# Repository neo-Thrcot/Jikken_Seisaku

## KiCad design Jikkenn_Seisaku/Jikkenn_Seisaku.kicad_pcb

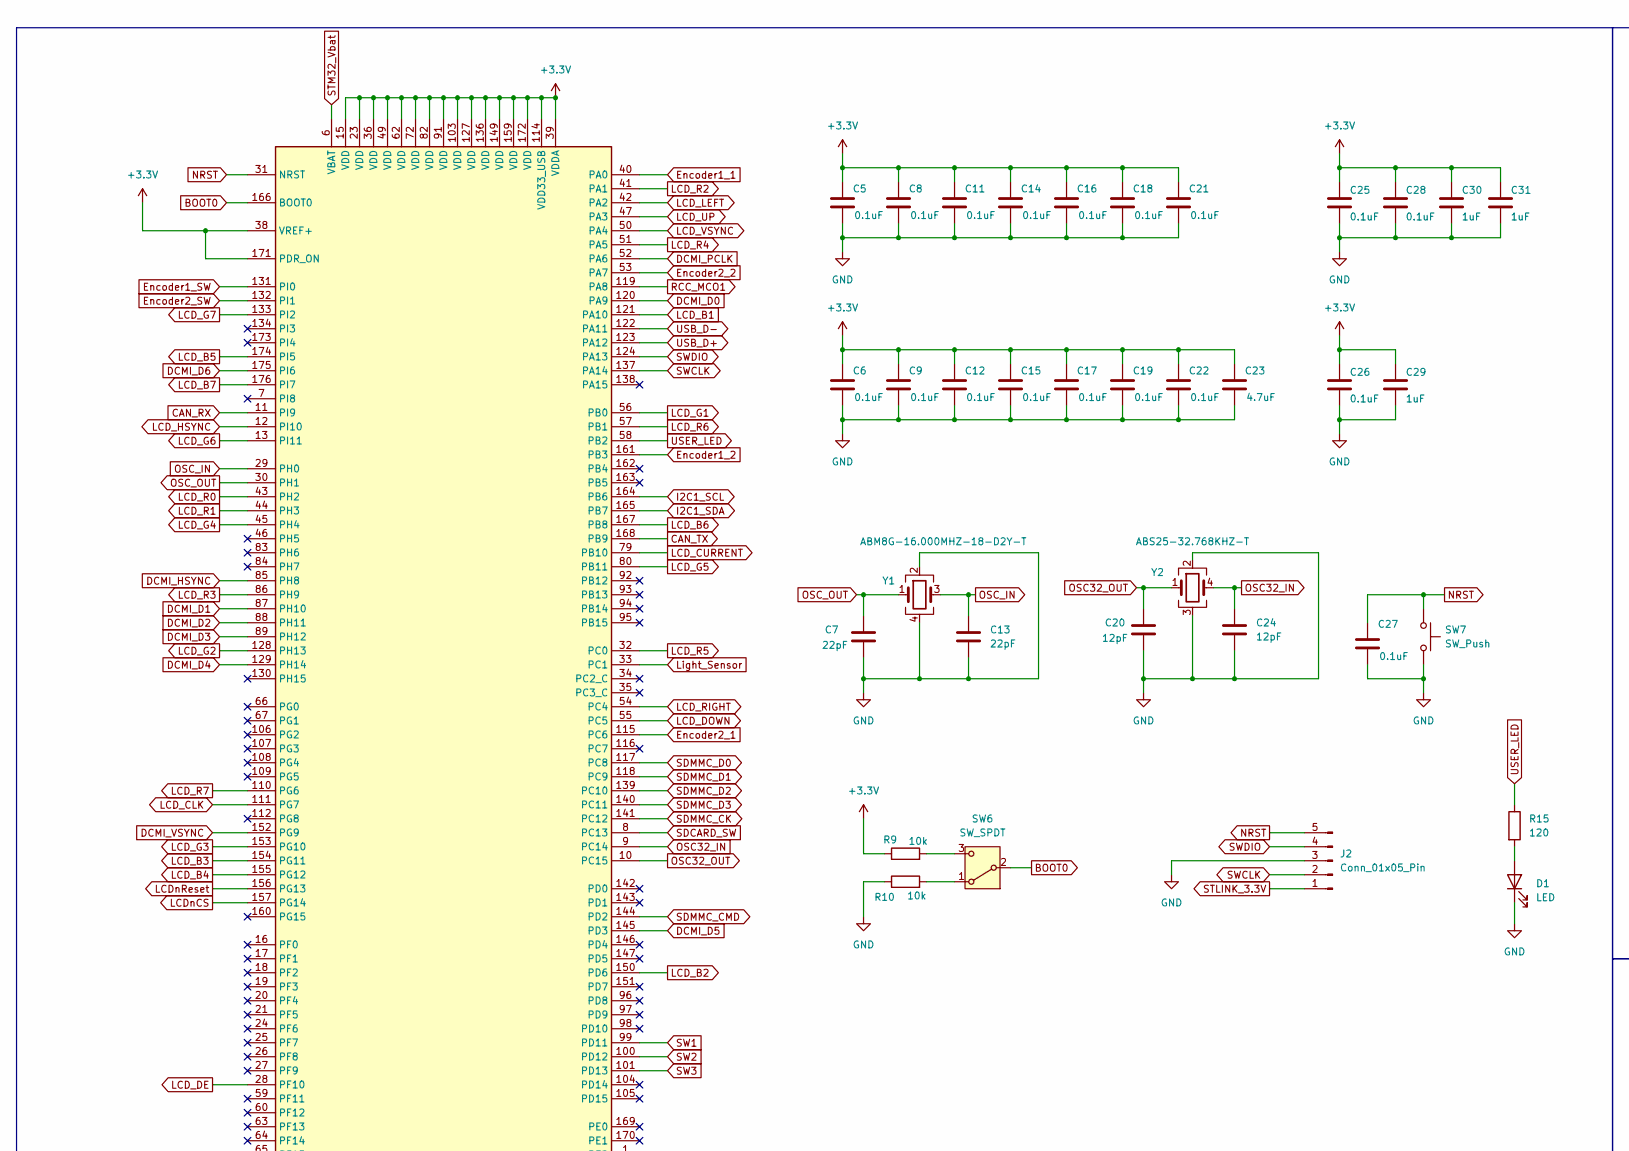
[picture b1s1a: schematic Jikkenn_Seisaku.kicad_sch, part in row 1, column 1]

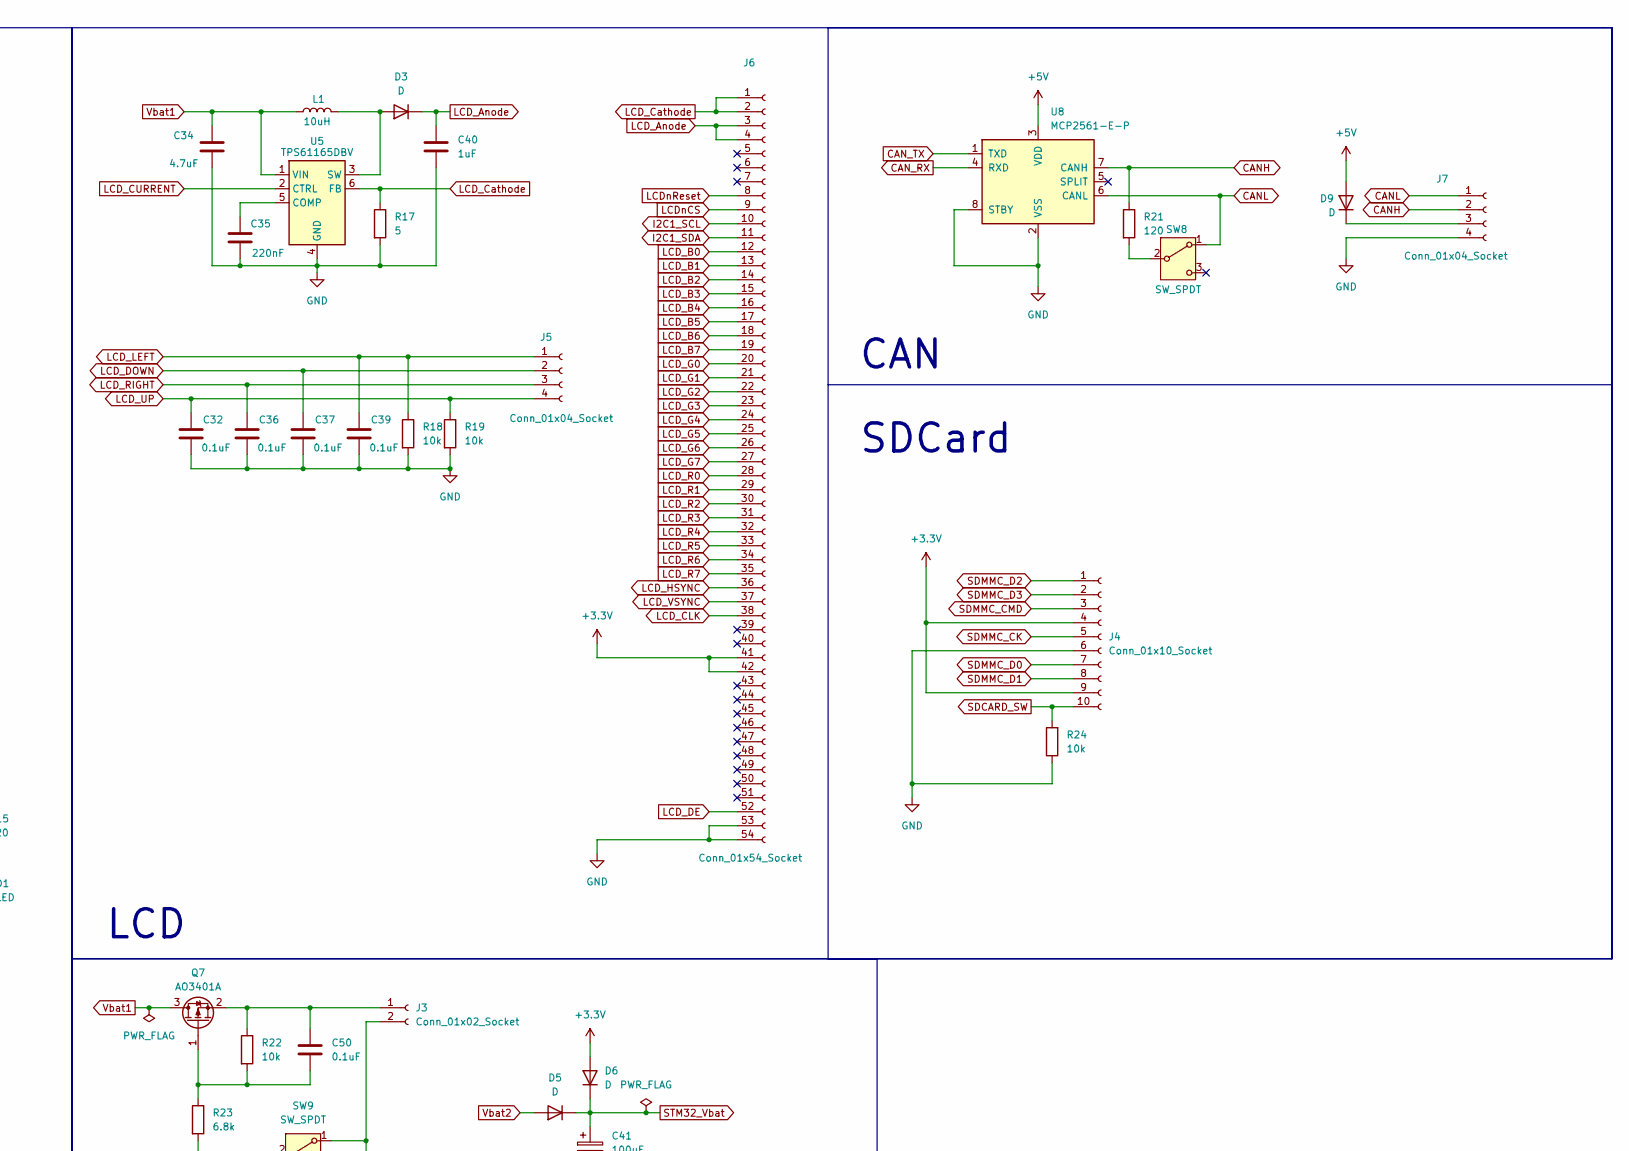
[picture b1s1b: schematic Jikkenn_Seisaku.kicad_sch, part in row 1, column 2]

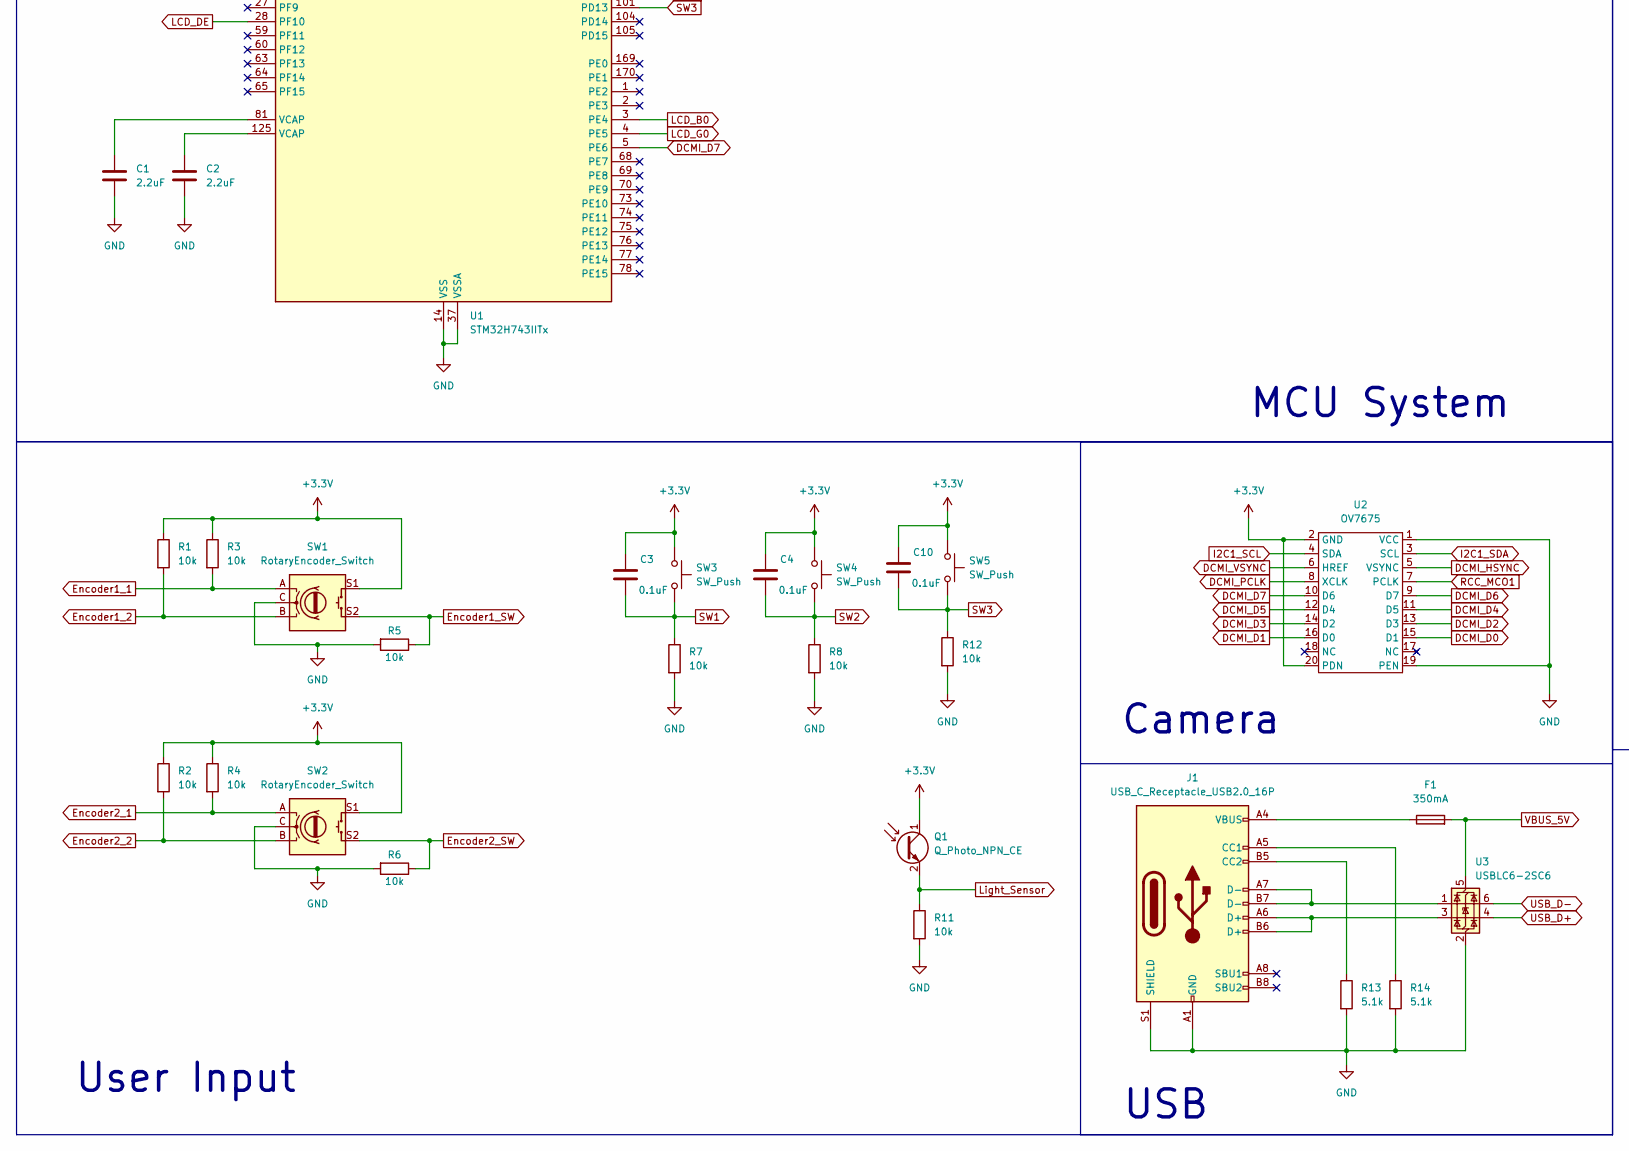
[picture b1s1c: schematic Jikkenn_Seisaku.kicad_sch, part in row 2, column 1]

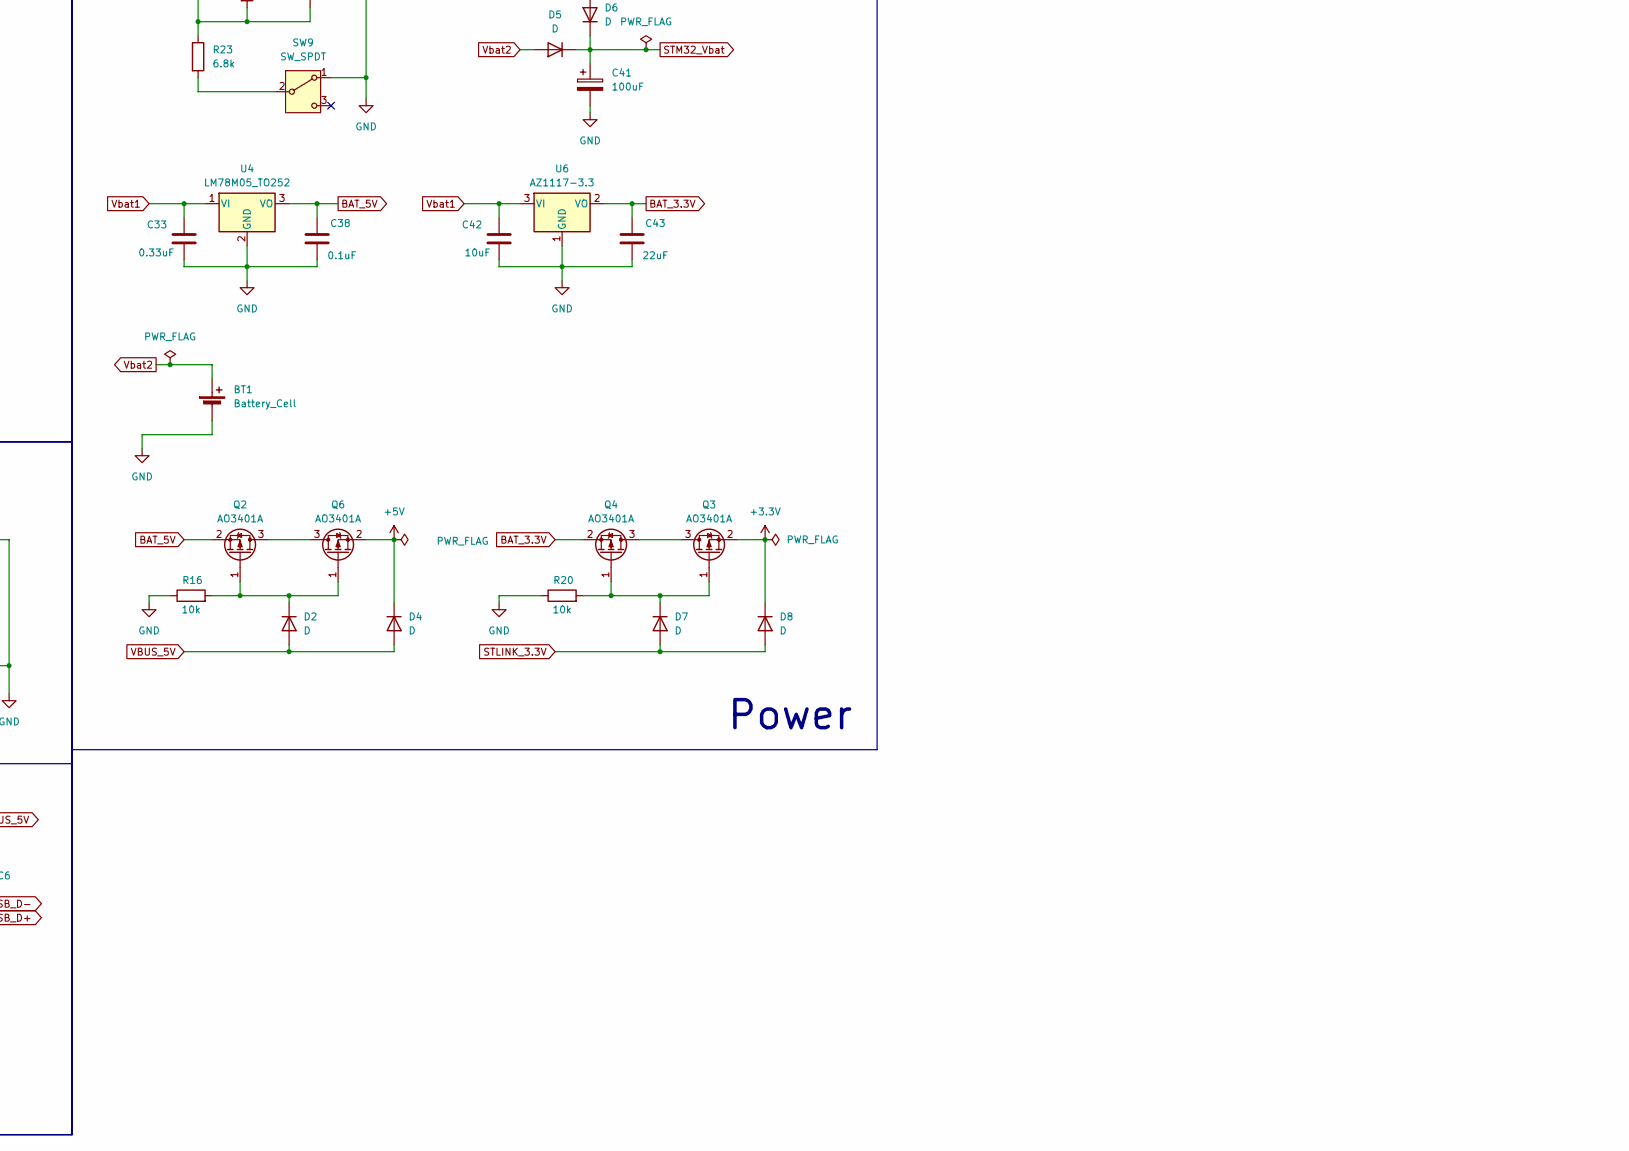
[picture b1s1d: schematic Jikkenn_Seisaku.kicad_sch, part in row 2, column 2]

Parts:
BT1: Battery_Cell; BatteryHolder_MYOUNG_BS-07-A1BJ001_CR2032
C1, C2: 2.2uF; C_0603_1608Metric_Pad1.08x0.95mm_HandSolder
C3, C4, C5, C6, C8, C9, C10, C11, C12, C14, C15, C16, C17, C18, C19, C21, C22, C25, C26, C27, C28, C32, C36, C37, C38, C39, C50: 0.1uF; C_0603_1608Metric_Pad1.08x0.95mm_HandSolder
C7, C13: 22pF; C_0603_1608Metric_Pad1.08x0.95mm_HandSolder
C20, C24: 12pF; C_0603_1608Metric_Pad1.08x0.95mm_HandSolder
C23, C34: 4.7uF; C_0603_1608Metric_Pad1.08x0.95mm_HandSolder
C29, C30, C31, C40: 1uF; C_0603_1608Metric_Pad1.08x0.95mm_HandSolder
C33: 0.33uF; C_0603_1608Metric_Pad1.08x0.95mm_HandSolder
C35: 220nF; C_0603_1608Metric_Pad1.08x0.95mm_HandSolder
C41: 100uF; CP_Elec_6.3x5.4_Nichicon
C42: 10uF; C_0603_1608Metric_Pad1.08x0.95mm_HandSolder
C43: 22uF; C_0603_1608Metric_Pad1.08x0.95mm_HandSolder
D1: LED; LED_0603_1608Metric_Pad1.05x0.95mm_HandSolder
D2, D3, D4, D5, D6, D7, D8, D9: D; D_TUMD2
F1: 350mA; Fuse_2010_5025Metric_Pad1.52x2.65mm_HandSolder
J1: USB_C_Receptacle_USB2.0_16P; USB_C_Receptacle_XKB_U262-16XN-4BVC11
J2: Conn_01x05_Pin; JST_XH_S5B-XH-A-1_1x05_P2.50mm_Horizontal
J3: Conn_01x02_Socket; JST_XH_S2B-XH-A_1x02_P2.50mm_Horizontal
J4: Conn_01x10_Socket; PinSocket_1x10_P2.54mm_Vertical
J5: Conn_01x04_Socket; Molex_200528-0040_1x04-1MP_P1.00mm_Horizontal
J6: Conn_01x54_Socket; Amphenol_F32Q-1A7x1-11054_1x54-1MP_P0.5mm_Horizontal
J7: Conn_01x04_Socket; JST_XH_S4B-XH-A-1_1x04_P2.50mm_Horizontal
L1: 10uH; LQH43PN100M26L
Q1: Q_Photo_NPN_CE; NJL7502
Q2, Q3, Q4, Q6, Q7: AO3401A; SOT-23
R1, R2, R3, R4, R5, R6, R7, R8, R9, R10, R11, R12, R16, R18, R19, R20, R22, R24: 10k; R_0603_1608Metric_Pad0.98x0.95mm_HandSolder
R13, R14: 5.1k; R_0603_1608Metric_Pad0.98x0.95mm_HandSolder
R15, R21: 120; R_0603_1608Metric_Pad0.98x0.95mm_HandSolder
R17: 5; R_0603_1608Metric_Pad0.98x0.95mm_HandSolder
R23: 6.8k; R_0603_1608Metric_Pad0.98x0.95mm_HandSolder
SW1, SW2: RotaryEncoder_Switch; RE111F-4S1-152S4-15P-A
SW3, SW4, SW5, SW7: SW_Push; SW_PUSH_6mm
SW6, SW8, SW9: SW_SPDT; PinSocket_1x03_P2.54mm_Vertical
U1: STM32H743IITx; LQFP-176_24x24mm_P0.5mm
U2: OV7675; PinSocket_2x10_P2.54mm_Vertical
U3: USBLC6-2SC6; SOT-23-6
U4: LM78M05_TO252; TO-252-2
U5: TPS61165DBV; SOT-23-6
U6: AZ1117-3.3; SOT-223-3_TabPin2
U8: MCP2561-E-P; DIP-8_W7.62mm
Y1: ABM8G-16.000MHZ-18-D2Y-T; Crystal_SMD_Abracon_ABM8G-4Pin_3.2x2.5mm
Y2: ABS25-32.768KHZ-T; Crystal_SMD_Abracon_ABS25-4Pin_8.0x3.8mm

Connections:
+3.3V: C3.1, C4.1, C5.1, C6.1, C8.1, C9.1, C10.1, C11.1, C12.1, C14.1, C15.1, C16.1, C17.1, C18.1, C19.1, C21.1, C22.1, C23.1, C25.1, C26.1, C28.1, C29.1, C30.1, C31.1, D6.2 (A), D8.1 (K), J4.4, J4.9, J6.41, J6.42, Q1.1 (C), Q3.2 (S), R1.1, R2.1, R3.1, R4.1, R9.1, SW1.S1, SW2.S1, SW3.1, SW4.1, SW5.1, U1.15 (VDD), U1.23 (VDD), U1.36 (VDD), U1.38 (VREF+), U1.39 (VDDA), U1.49 (VDD), U1.62 (VDD), U1.72 (VDD), U1.82 (VDD), U1.91 (VDD), U1.103 (VDD), U1.114 (VDD33_USB), U1.127 (VDD), U1.136 (VDD), U1.149 (VDD), U1.159 (VDD), U1.171 (PDR_ON), U1.172 (VDD), U2.2 (GND), U2.20 (PDN)
+5V: D4.1 (K), D9.2 (A), Q6.2 (S), U8.3 (VDD)
BAT_3.3V: C43.1, Q4.2 (S), U6.2 (VO)
BAT_5V: C38.1, Q2.2 (S), U4.3 (VO)
BOOT0: SW6.2 (B), U1.166 (BOOT0)
CANH: J7.2, R21.1, U8.7 (CANH)
CANL: J7.1, SW8.1 (A), U8.6 (CANL)
CAN_RX: U1.11 (PI9), U8.4 (RXD)
CAN_TX: U1.168 (PB9), U8.1 (TXD)
DCMI_D0: U1.120 (PA9), U2.15 (D1)
DCMI_D1: U1.87 (PH10), U2.16 (D0)
DCMI_D2: U1.88 (PH11), U2.13 (D3)
DCMI_D3: U1.89 (PH12), U2.14 (D2)
DCMI_D4: U1.129 (PH14), U2.11 (D5)
DCMI_D5: U1.145 (PD3), U2.12 (D4)
DCMI_D6: U1.175 (PI6), U2.9 (D7)
DCMI_D7: U1.5 (PE6), U2.10 (D6)
DCMI_HSYNC: U1.85 (PH8), U2.5 (VSYNC)
DCMI_PCLK: U1.52 (PA6), U2.8 (XCLK)
DCMI_VSYNC: U1.152 (PG9), U2.6 (HREF)
Encoder1_1: R3.2, SW1.A, U1.40 (PA0)
Encoder1_2: R1.2, SW1.B, U1.161 (PB3)
Encoder1_SW: R5.1, SW1.S2, U1.131 (PI0)
Encoder2_1: R4.2, SW2.A, U1.115 (PC6)
Encoder2_2: R2.2, SW2.B, U1.53 (PA7)
Encoder2_SW: R6.1, SW2.S2, U1.132 (PI1)
GND: BT1.2 (-), C1.2, C2.2, C5.2, C6.2, C7.2, C8.2, C9.2, C11.2, C12.2, C13.2, C14.2, C15.2, C16.2, C17.2, C18.2, C19.2, C20.2, C21.2, C22.2, C23.2, C24.2, C25.2, C26.2, C27.2, C28.2, C29.2, C30.2, C31.2, C32.2, C33.2, C34.2, C35.2, C36.2, C37.2, C38.2, C39.2, C40.2, C41.2, C42.2, C43.2, D1.1 (K), J1.A1 (GND), J1.A12 (GND), J1.B1 (GND), J1.B12 (GND), J1.S1 (SHIELD), J2.3, J3.2, J4.6, J6.53, J6.54, J7.4, R5.2, R6.2, R7.2, R8.2, R10.1, R11.2, R12.2, R13.2, R14.2, R16.1, R17.2, R18.2, R19.2, R20.1, R24.1, SW1.C, SW2.C, SW7.2, SW9.1 (A), U1.14 (VSS), U1.22 (VSS), U1.37 (VSSA), U1.48 (VSS), U1.61 (VSS), U1.71 (VSS), U1.90 (VSS), U1.102 (VSS), U1.113 (VSS), U1.126 (VSS), U1.135 (VSS), U1.148 (VSS), U1.158 (VSS), U2.1 (VCC), U2.19 (PEN), U3.2 (GND), U4.2 (GND), U5.4 (GND), U6.1 (GND), U8.2 (VSS), U8.8 (STBY), Y1.2, Y1.4, Y2.2, Y2.3
I2C1_SCL: J6.10, U1.164 (PB6), U2.4 (SDA)
I2C1_SDA: J6.11, U1.165 (PB7), U2.3 (SCL)
LCD_Anode: C40.1, D3.1 (K), J6.3, J6.4
LCD_B0: J6.12, U1.3 (PE4)
LCD_B1: J6.13, U1.121 (PA10)
LCD_B2: J6.14, U1.150 (PD6)
LCD_B3: J6.15, U1.154 (PG11)
LCD_B4: J6.16, U1.155 (PG12)
LCD_B5: J6.17, U1.174 (PI5)
LCD_B6: J6.18, U1.167 (PB8)
LCD_B7: J6.19, U1.176 (PI7)
LCD_CLK: J6.38, U1.111 (PG7)
LCD_CURRENT: U1.79 (PB10), U5.2 (CTRL)
LCD_Cathode: J6.1, J6.2, R17.1, U5.6 (FB)
LCD_DE: J6.52, U1.28 (PF10)
LCD_DOWN: C37.1, J5.2, U1.55 (PC5)
LCD_G0: J6.20, U1.4 (PE5)
LCD_G1: J6.21, U1.56 (PB0)
LCD_G2: J6.22, U1.128 (PH13)
LCD_G3: J6.23, U1.153 (PG10)
LCD_G4: J6.24, U1.45 (PH4)
LCD_G5: J6.25, U1.80 (PB11)
LCD_G6: J6.26, U1.13 (PI11)
LCD_G7: J6.27, U1.133 (PI2)
LCD_HSYNC: J6.36, U1.12 (PI10)
LCD_LEFT: C39.1, J5.1, R18.1, U1.42 (PA2)
LCD_R0: J6.28, U1.43 (PH2)
LCD_R1: J6.29, U1.44 (PH3)
LCD_R2: J6.30, U1.41 (PA1)
LCD_R3: J6.31, U1.86 (PH9)
LCD_R4: J6.32, U1.51 (PA5)
LCD_R5: J6.33, U1.32 (PC0)
LCD_R6: J6.34, U1.57 (PB1)
LCD_R7: J6.35, U1.110 (PG6)
LCD_RIGHT: C36.1, J5.3, U1.54 (PC4)
LCD_UP: C32.1, J5.4, R19.1, U1.47 (PA3)
LCD_VSYNC: J6.37, U1.50 (PA4)
LCDnCS: J6.9, U1.157 (PG14)
LCDnReset: J6.8, U1.156 (PG13)
Light_Sensor: Q1.2 (E), R11.1, U1.33 (PC1)
NRST: C27.1, J2.5, SW7.1, U1.31 (NRST)
unnamed: C1.1, U1.81 (VCAP)
unnamed: C2.1, U1.125 (VCAP)
unnamed: D1.2 (A), R15.2
unnamed: D2.1 (K), Q2.1 (G), Q6.1 (G), R16.2
unnamed: D3.2 (A), L1.2, U5.3 (SW)
unnamed: D7.1 (K), Q3.1 (G), Q4.1 (G), R20.2
unnamed: D9.1 (K), J7.3
unnamed: F1.1, J1.A4 (VBUS), J1.A9 (VBUS), J1.B4 (VBUS), J1.B9 (VBUS)
unnamed: J1.A5 (CC1), R14.1
unnamed: J1.B5 (CC2), R13.1
unnamed: J1.A6 (D+), J1.B6 (D+), U3.3 (I/O2)
unnamed: J1.A7 (D-), J1.B7 (D-), U3.1 (I/O1)
unnamed: C50.1, J3.1, Q7.2 (S), R22.1
unnamed: Q2.3 (D), Q6.3 (D)
unnamed: Q3.3 (D), Q4.3 (D)
unnamed: C50.2, Q7.1 (G), R22.2, R23.1
unnamed: R10.2, SW6.1 (A)
unnamed: R9.2, SW6.3 (C)
unnamed: R21.2, SW8.2 (B)
unnamed: R23.2, SW9.2 (B)
unnamed: C35.1, U5.5 (COMP)
OSC32_IN: C24.1, U1.9 (PC14), Y2.4
OSC32_OUT: C20.1, U1.10 (PC15), Y2.1
OSC_IN: C13.1, U1.29 (PH0), Y1.3
OSC_OUT: C7.1, U1.30 (PH1), Y1.1
RCC_MCO1: U1.119 (PA8), U2.7 (PCLK)
SDCARD_SW: J4.10, R24.2, U1.8 (PC13)
SDMMC_CK: J4.5, U1.141 (PC12)
SDMMC_CMD: J4.3, U1.144 (PD2)
SDMMC_D0: J4.7, U1.117 (PC8)
SDMMC_D1: J4.8, U1.118 (PC9)
SDMMC_D2: J4.1, U1.139 (PC10)
SDMMC_D3: J4.2, U1.140 (PC11)
STLINK_3.3V: D7.2 (A), D8.2 (A), J2.1
STM32_Vbat: C41.1, D5.1 (K), D6.1 (K), U1.6 (VBAT)
SW1: C3.2, R7.1, SW3.2, U1.99 (PD11)
SW2: C4.2, R8.1, SW4.2, U1.100 (PD12)
SW3: C10.2, R12.1, SW5.2, U1.101 (PD13)
SWCLK: J2.2, U1.137 (PA14)
SWDIO: J2.4, U1.124 (PA13)
USB_D+: U1.123 (PA12), U3.4 (I/O2)
USB_D-: U1.122 (PA11), U3.6 (I/O1)
USER_LED: R15.1, U1.58 (PB2)
VBUS_5V: D2.2 (A), D4.2 (A), F1.2, U3.5 (VBUS)
Vbat1: C33.1, C34.1, C42.1, L1.1, Q7.3 (D), U4.1 (VI), U5.1 (VIN), U6.3 (VI)
Vbat2: BT1.1 (+), D5.2 (A)

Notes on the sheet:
CAN
Power
User Input
MCU System
LCD
SDCard
USB
Camera

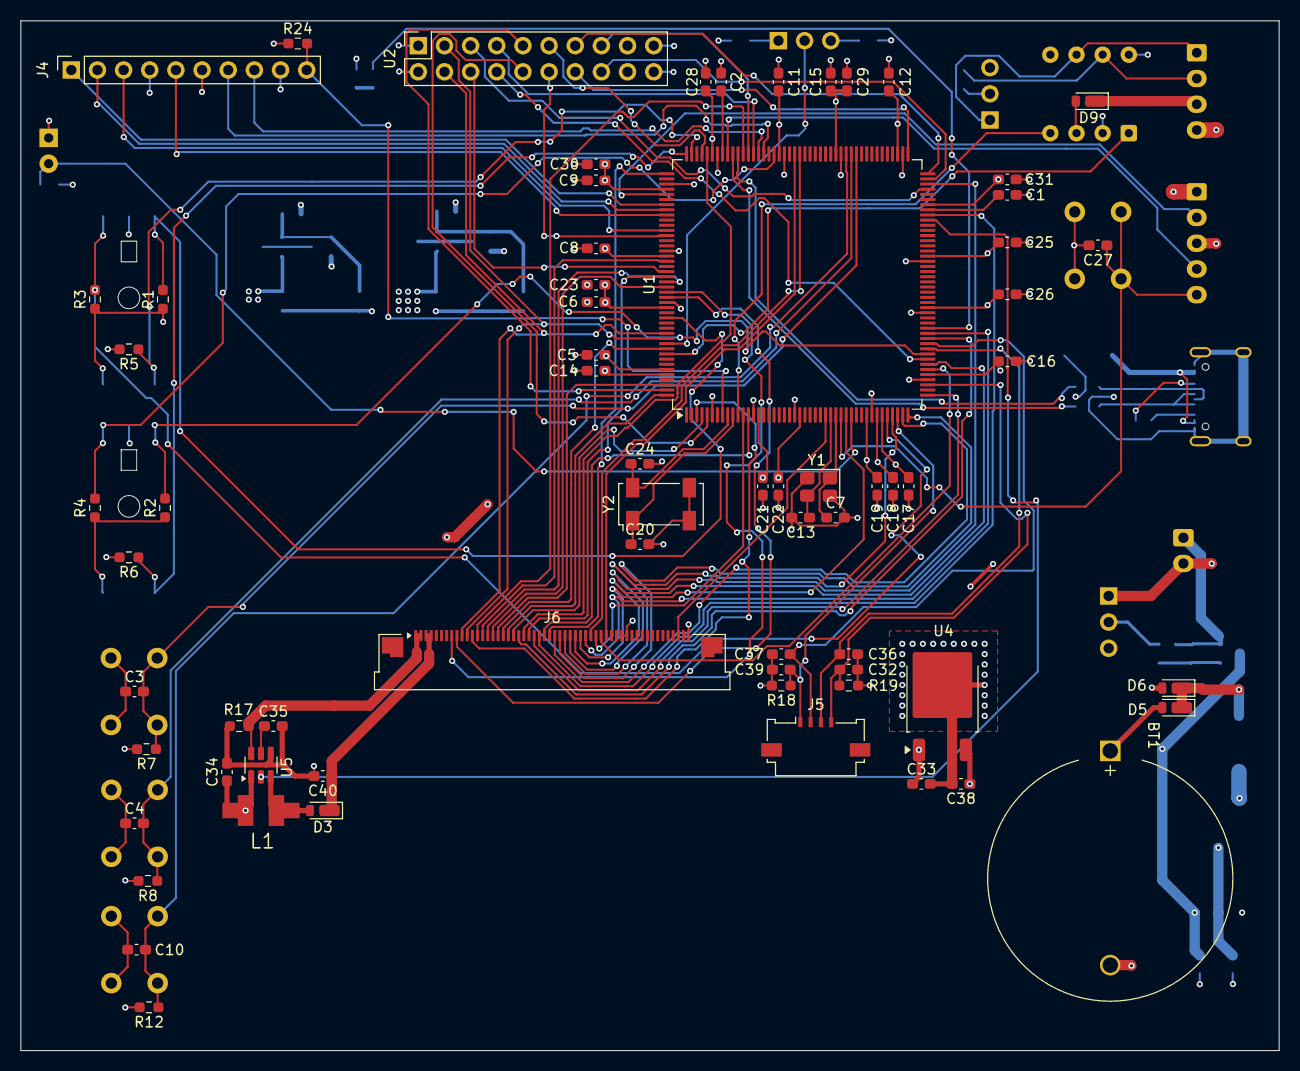
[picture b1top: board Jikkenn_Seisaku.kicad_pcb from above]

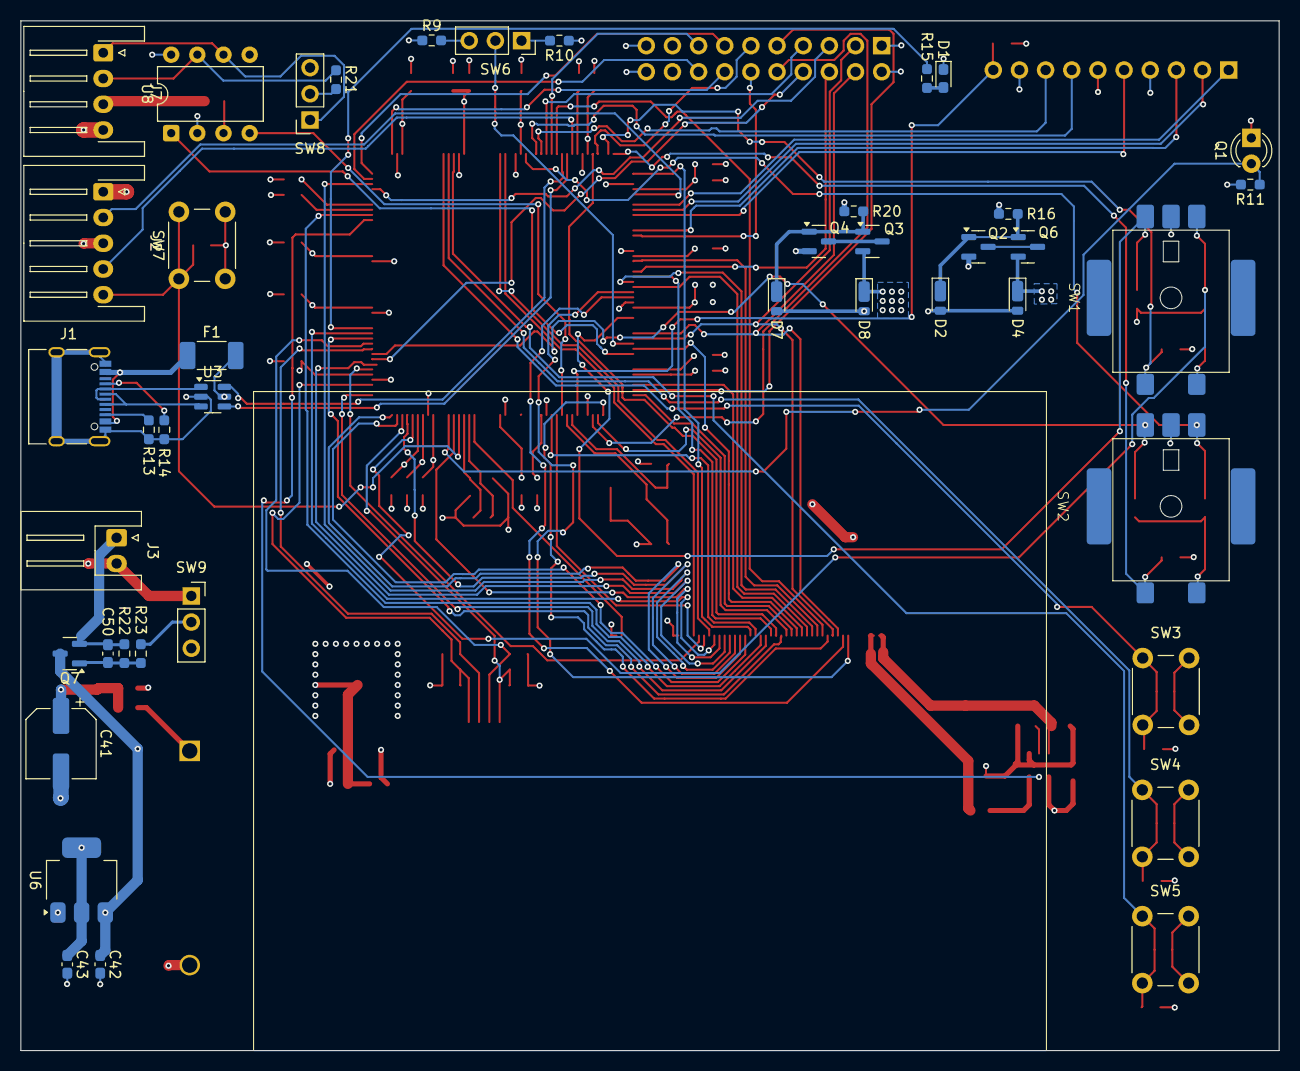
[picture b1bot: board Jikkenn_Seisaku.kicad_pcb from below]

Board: 4 copper layers, 122.2 x 100.0 mm, 111 parts (43 on the bottom side), 114 nets.

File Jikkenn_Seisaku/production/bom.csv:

Designator,Footprint,Quantity,Value,LCSC Part #
BT1,BatteryHolder_MYOUNG_BS-07-A1BJ001_CR2032,1,Battery_Cell,
"C1, C2",0603,2,2.2uF,
"C10, C11, C12, C14, C15, C16, C17, C18, C19, C21, C22, C25, C26, C27, C28, C3, C32, C36, C37, C38, C39, C4, C5, C50, C6, C8, C9",0603,27,0.1uF,
"C13, C7",0603,2,22pF,
"C20, C24",0603,2,12pF,
"C23, C34",0603,2,4.7uF,
"C29, C30, C31, C40",0603,4,1uF,
C33,0603,1,0.33uF,
C35,0603,1,220nF,
C41,CP_Elec_6.3x5.4_Nichicon,1,100uF,
C42,0603,1,10uF,
C43,0603,1,22uF,
D1,0603,1,LED,
"D2, D3, D4, D5, D6, D7, D8, D9",D_TUMD2,8,D,
F1,2010,1,350mA,
J1,USB_C_Receptacle_XKB_U262-16XN-4BVC11,1,USB_C_Receptacle_USB2.0_16P,
J2,JST_XH_S5B-XH-A-1_1x05_P2.50mm_Horizontal,1,Conn_01x05_Pin,
J3,JST_XH_S2B-XH-A_1x02_P2.50mm_Horizontal,1,Conn_01x02_Socket,
J4,PinSocket_1x10_P2.54mm_Vertical,1,Conn_01x10_Socket,
J5,Molex_200528-0040_1x04-1MP_P1.00mm_Horizontal,1,Conn_01x04_Socket,
J6,Amphenol_F32Q-1A7x1-11054_1x54-1MP_P0.5mm_Horizontal,1,Conn_01x54_Socket,
J7,JST_XH_S4B-XH-A-1_1x04_P2.50mm_Horizontal,1,Conn_01x04_Socket,
L1,LQH43PN100M26L,1,10uH,
Q1,NJL7502,1,Q_Photo_NPN_CE,
"Q2, Q3, Q4, Q6, Q7",SOT-23,5,AO3401A,
"R1, R10, R11, R12, R16, R18, R19, R2, R20, R22, R24, R3, R4, R5, R6, R7, R8, R9",0603,18,10k,
"R13, R14",0603,2,5.1k,
"R15, R21",0603,2,120,
R17,0603,1,5,
R23,0603,1,6.8k,
"SW1, SW2",RE111F-4S1-152S4-15P-A,2,RotaryEncoder_Switch,
"SW3, SW4, SW5, SW7",SW_PUSH_6mm,4,SW_Push,
"SW6, SW8, SW9",PinSocket_1x03_P2.54mm_Vertical,3,SW_SPDT,
U1,LQFP-176_24x24mm_P0.5mm,1,STM32H743IITx,
U2,PinSocket_2x10_P2.54mm_Vertical,1,OV7675,
U3,SOT-23-6,1,USBLC6-2SC6,
U4,TO-252-2,1,LM78M05_TO252,
U5,SOT-23-6,1,TPS61165DBV,
U6,SOT-223-3_TabPin2,1,AZ1117-3.3,
U8,DIP-8_W7.62mm,1,MCP2561-E-P,
Y1,Crystal_SMD_Abracon_ABM8G-4Pin_3.2x2.5mm,1,ABM8G-16.000MHZ-18-D2Y-T,
Y2,Crystal_SMD_Abracon_ABS25-4Pin_8.0x3.8mm,1,ABS25-32.768KHZ-T,

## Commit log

2026-02-03 Add Circuit Project
